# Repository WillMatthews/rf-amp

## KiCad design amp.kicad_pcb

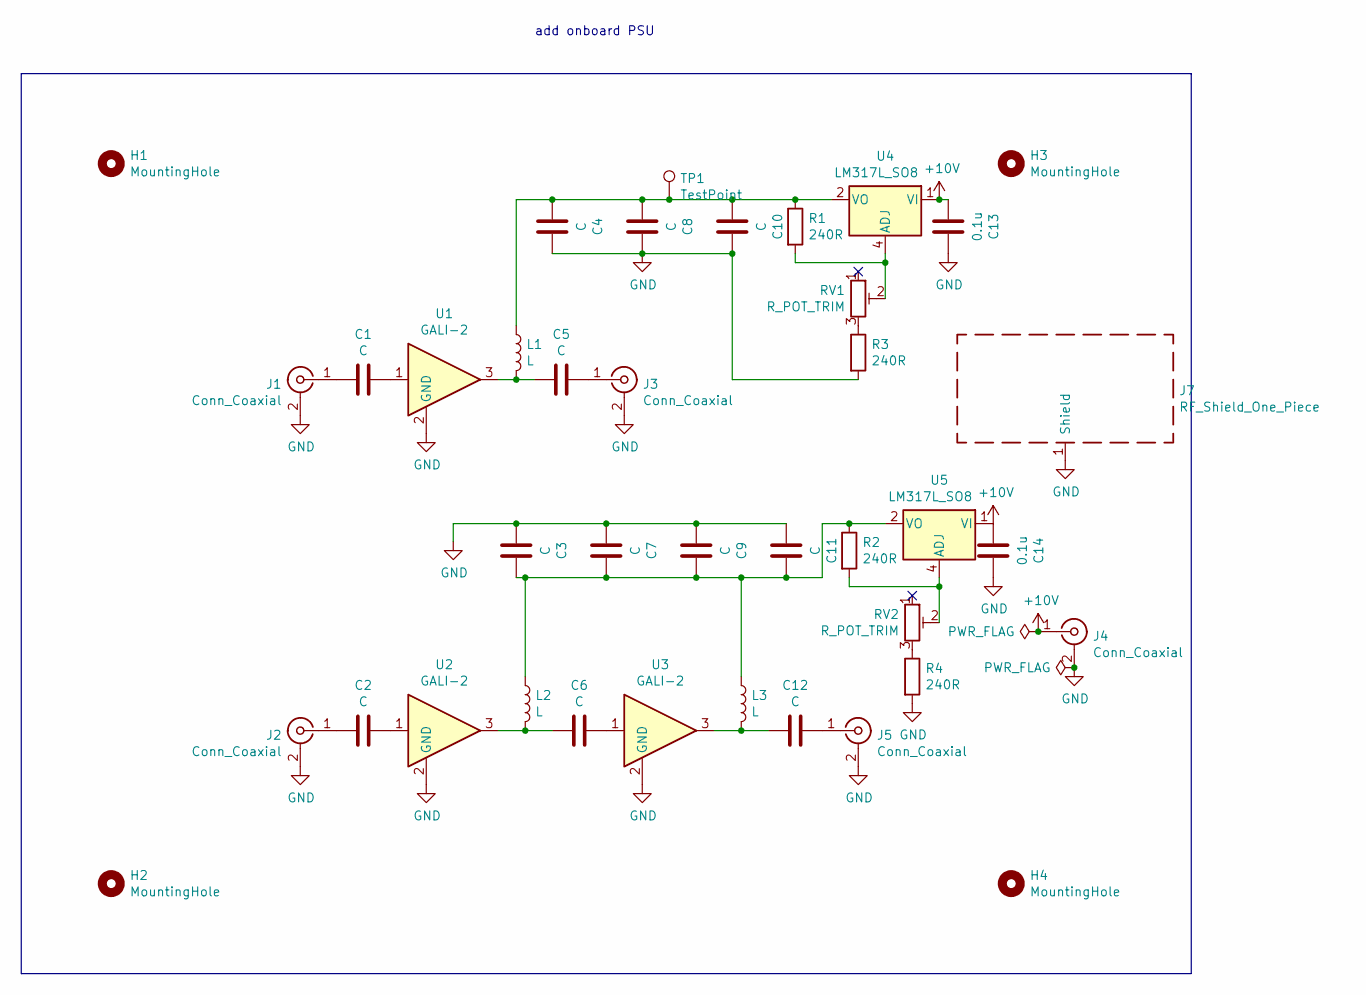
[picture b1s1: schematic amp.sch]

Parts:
C1, C2, C5, C6, C12: C; C_0402_1005Metric
C3, C4: C; C_0805_2012Metric
C7, C8, C9, C10, C11: C; C_0603_1608Metric
C13, C14: 0.1u; C_0805_2012Metric_Pad1.15x1.40mm_HandSolder
H1, H2, H3, H4: MountingHole; MountingHole_4.3mm_M4
J1, J2, J3, J4, J5: Conn_Coaxial; SMA_Amphenol_132289_EdgeMount
J7: RF_Shield_One_Piece; Laird_Technologies_BMI-S-230-F_50.8x38.1mm
L1, L2, L3: L; GU1604
R1, R2, R3, R4: 240R; R_0805_2012Metric
RV1, RV2: R_POT_TRIM; Potentiometer_Bourns_3314G_Vertical
TP1: TestPoint; TestPoint_Pad_D2.0mm
U1, U2, U3: GALI-2; SOT-89-3
U4, U5: LM317L_SO8; SOIC-8_3.9x4.9mm_P1.27mm

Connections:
+10V: C13.2, C14.2, J4.1 (In), U4.1 (VI), U5.1 (VI)
GND: C3.2, C4.1, C7.2, C8.1, C9.2, C10.1, C11.2, C13.1, C14.1, J1.2 (Ext), J2.2 (Ext), J3.2 (Ext), J4.2 (Ext), J5.2 (Ext), J7.1, R3.2, R4.2, U1.2 (GND), U2.2 (GND), U3.2 (GND)
unnamed: C1.1, U1.1
unnamed: C1.2, J1.1 (In)
unnamed: C2.1, U2.1
unnamed: C2.2, J2.1 (In)
unnamed: C5.1, J3.1 (In)
unnamed: C5.2, L1.2, U1.3
unnamed: C6.1, U3.1
unnamed: C6.2, L2.2, U2.3
unnamed: C4.2, C8.2, C10.2, L1.1, R1.1, TP1.1, U4.2 (VO), U4.3 (VO), U4.6 (VO), U4.7 (VO)
unnamed: C3.1, C7.1, C9.1, C11.1, L2.1, L3.1, R2.1, U5.2 (VO), U5.3 (VO), U5.6 (VO), U5.7 (VO)
unnamed: C12.1, J5.1 (In)
unnamed: C12.2, L3.2, U3.3
unnamed: R1.2, RV1.2, U4.4 (ADJ)
unnamed: R2.2, RV2.2, U5.4 (ADJ)
unnamed: R3.1, RV1.3
unnamed: R4.1, RV2.3

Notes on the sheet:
add onboard PSU

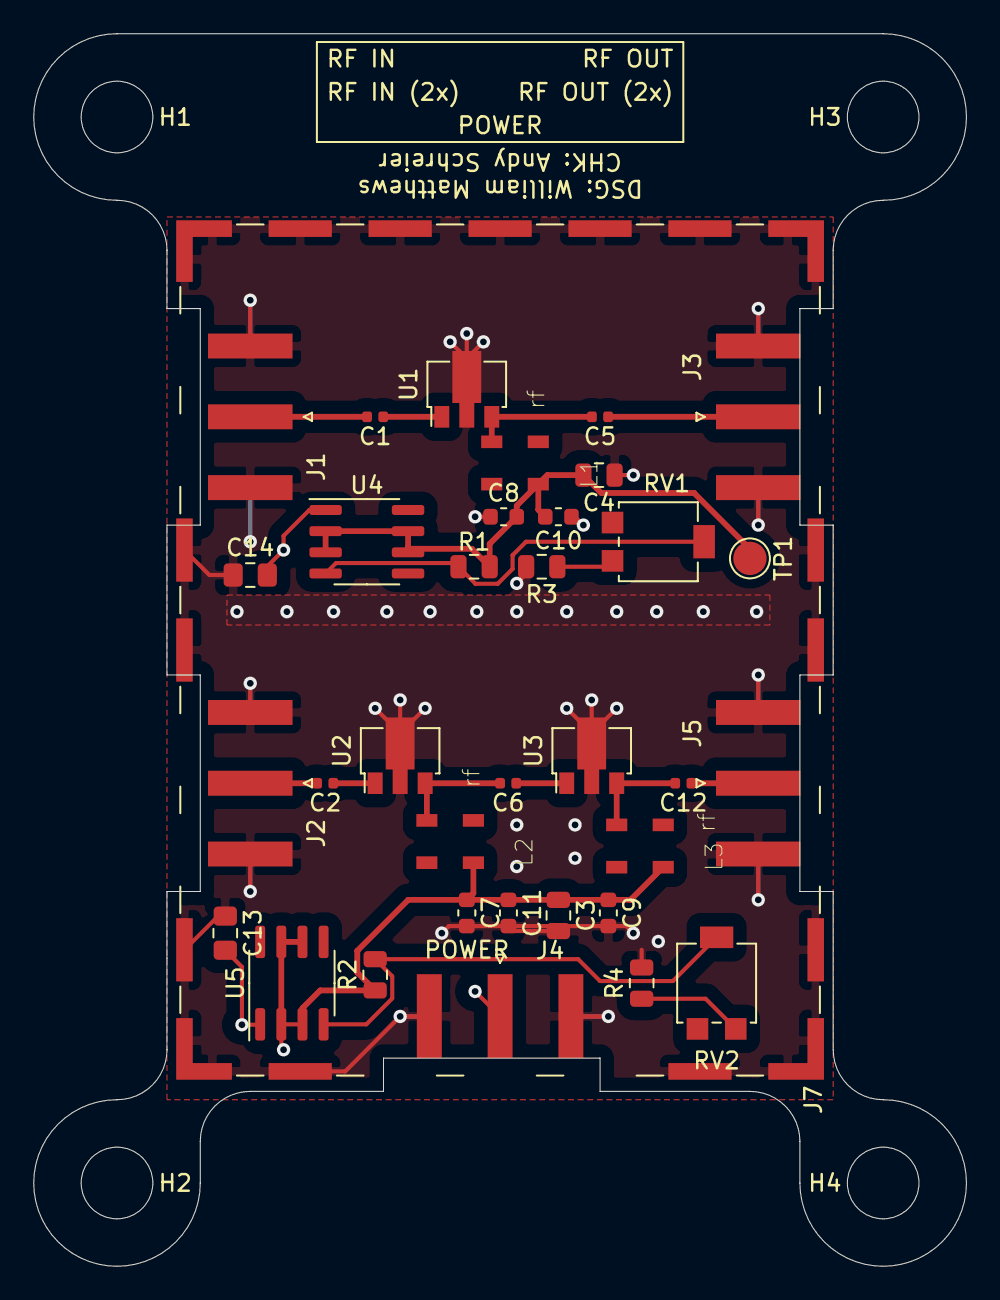
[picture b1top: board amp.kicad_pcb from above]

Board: 4 copper layers, 56.0 x 74.0 mm, 39 parts (0 on the bottom side), 18 nets.

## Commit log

2024-04-06 Create LICENSE
